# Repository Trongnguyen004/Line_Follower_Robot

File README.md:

# Line_Follower_Robot
## #Hình ảnh

<p align="center">
  <table>
      <td>
        
      </td>
      <td>
        
      </td>
    
  </table>
</p>

### *Cảm biến QTR8A được tham khảo tại: https://www.pololu.com/product/960

<p align="center">
  <table>
    <tr>
      <td>
        
      </td>
      <td>
        
      </td>  
    </tr>
  </table>
</p>

## #Video

### *Chạy Thử

https://github.com/Trongnguyen004/Line_Follower_Robot/assets/137270832/600d7f80-0cda-47ed-8069-f7d0e4e03a02

https://github.com/Trongnguyen004/Line_Follower_Robot/assets/137270832/67cb3d83-4516-45d8-a72a-21b8230ec6d9

### *Test cảm biến
https://github.com/Trongnguyen004/Line_Follower_Robot/assets/137270832/a73f50d7-3c18-4a8b-9868-28da99d4ba61

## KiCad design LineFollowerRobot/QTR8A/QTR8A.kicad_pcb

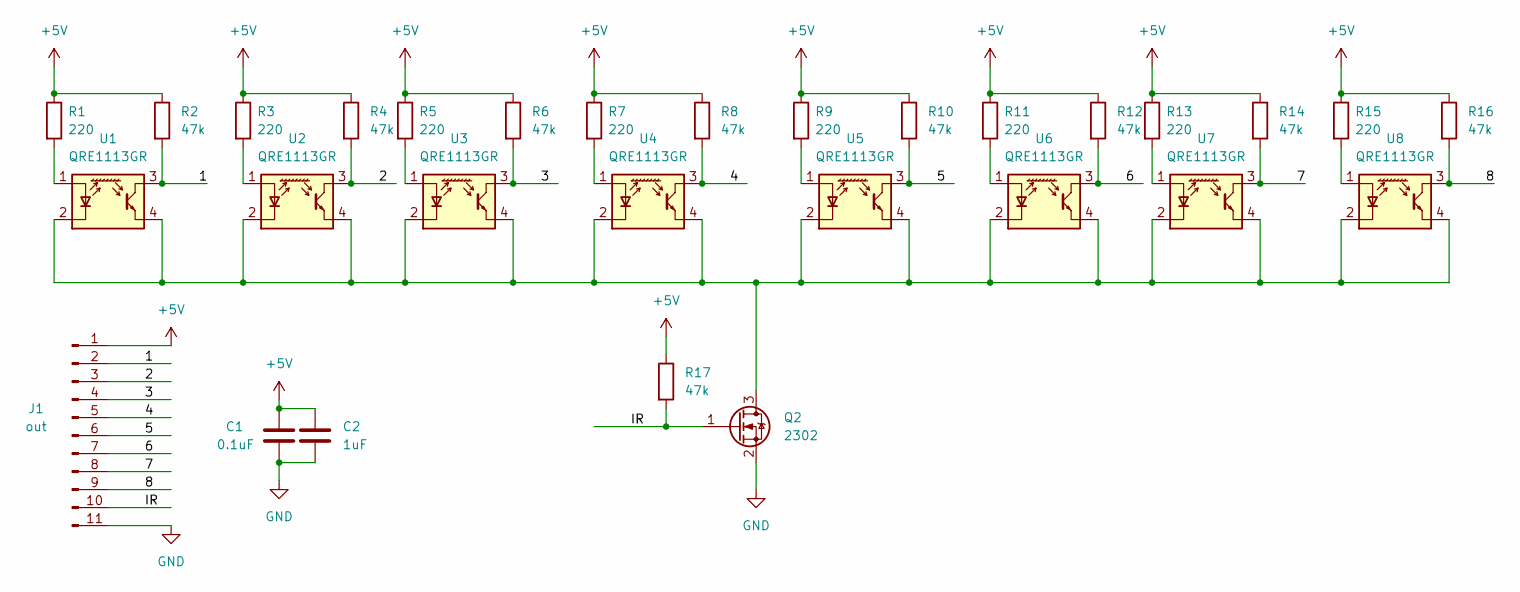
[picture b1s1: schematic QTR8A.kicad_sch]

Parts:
C1: 0.1uF; C_0805_2012Metric
C2: 1uF; C_0805_2012Metric
J1: out; PinHeader_1x11_P2.54mm_Vertical
Q2: 2302; SOT-23
R1, R3, R5, R7, R9, R11, R13, R15: 220; R_0603_1608Metric
R2, R4, R6, R8, R10, R12, R14, R16, R17: 47k; R_0603_1608Metric
U1, U2, U3, U4, U5, U6, U7, U8: QRE1113GR; OnSemi_CASE100CY

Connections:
+5V: C1.1, C2.1, J1.1, R1.1, R2.1, R3.1, R4.1, R5.1, R6.1, R7.1, R8.1, R9.1, R10.1, R11.1, R12.1, R13.1, R14.1, R15.1, R16.1, R17.1
/1: J1.2, R2.2, U1.3
/2: J1.3, R4.2, U2.3
/3: J1.4, R6.2, U3.3
/4: J1.5, R8.2, U4.3
/5: J1.6, R10.2, U5.3
/6: J1.7, R12.2, U6.3
/7: J1.8, R14.2, U7.3
/8: J1.9, R16.2, U8.3
/IR: J1.10, Q2.1 (G), R17.2
GND: C1.2, C2.2, J1.11, Q2.2 (S)
unnamed: Q2.3 (D), U1.2 (K), U1.4, U2.2 (K), U2.4, U3.2 (K), U3.4, U4.2 (K), U4.4, U5.2 (K), U5.4, U6.2 (K), U6.4, U7.2 (K), U7.4, U8.2 (K), U8.4
unnamed: R1.2, U1.1 (A)
unnamed: R3.2, U2.1 (A)
unnamed: R5.2, U3.1 (A)
unnamed: R7.2, U4.1 (A)
unnamed: R9.2, U5.1 (A)
unnamed: R11.2, U6.1 (A)
unnamed: R13.2, U7.1 (A)
unnamed: R15.2, U8.1 (A)

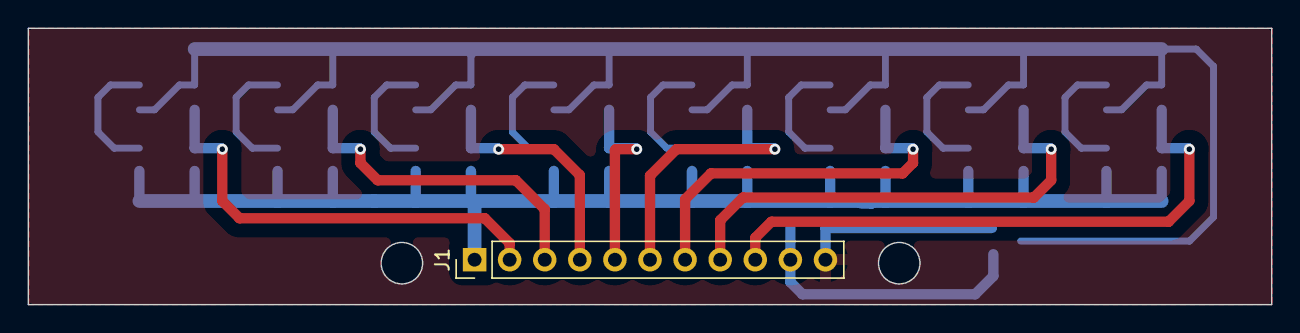
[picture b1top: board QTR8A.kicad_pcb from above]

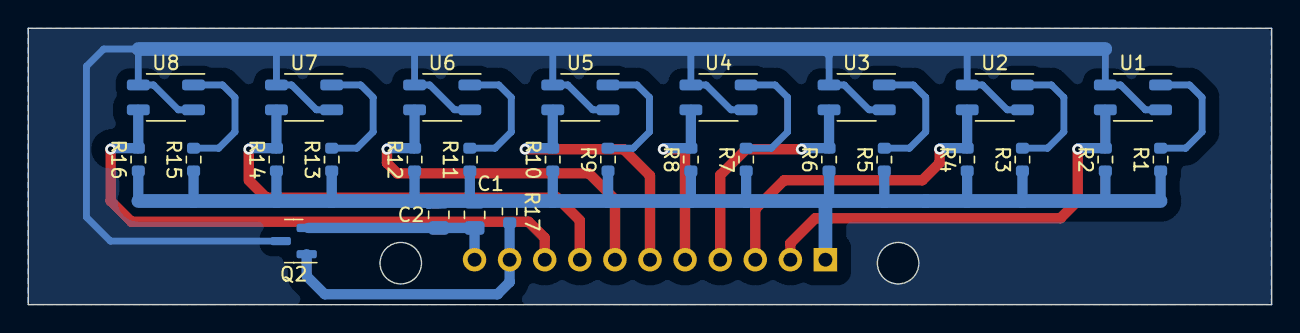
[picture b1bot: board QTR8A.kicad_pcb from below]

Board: 2 copper layers, 90.0 x 20.0 mm, 29 parts (28 on the bottom side), 20 nets.

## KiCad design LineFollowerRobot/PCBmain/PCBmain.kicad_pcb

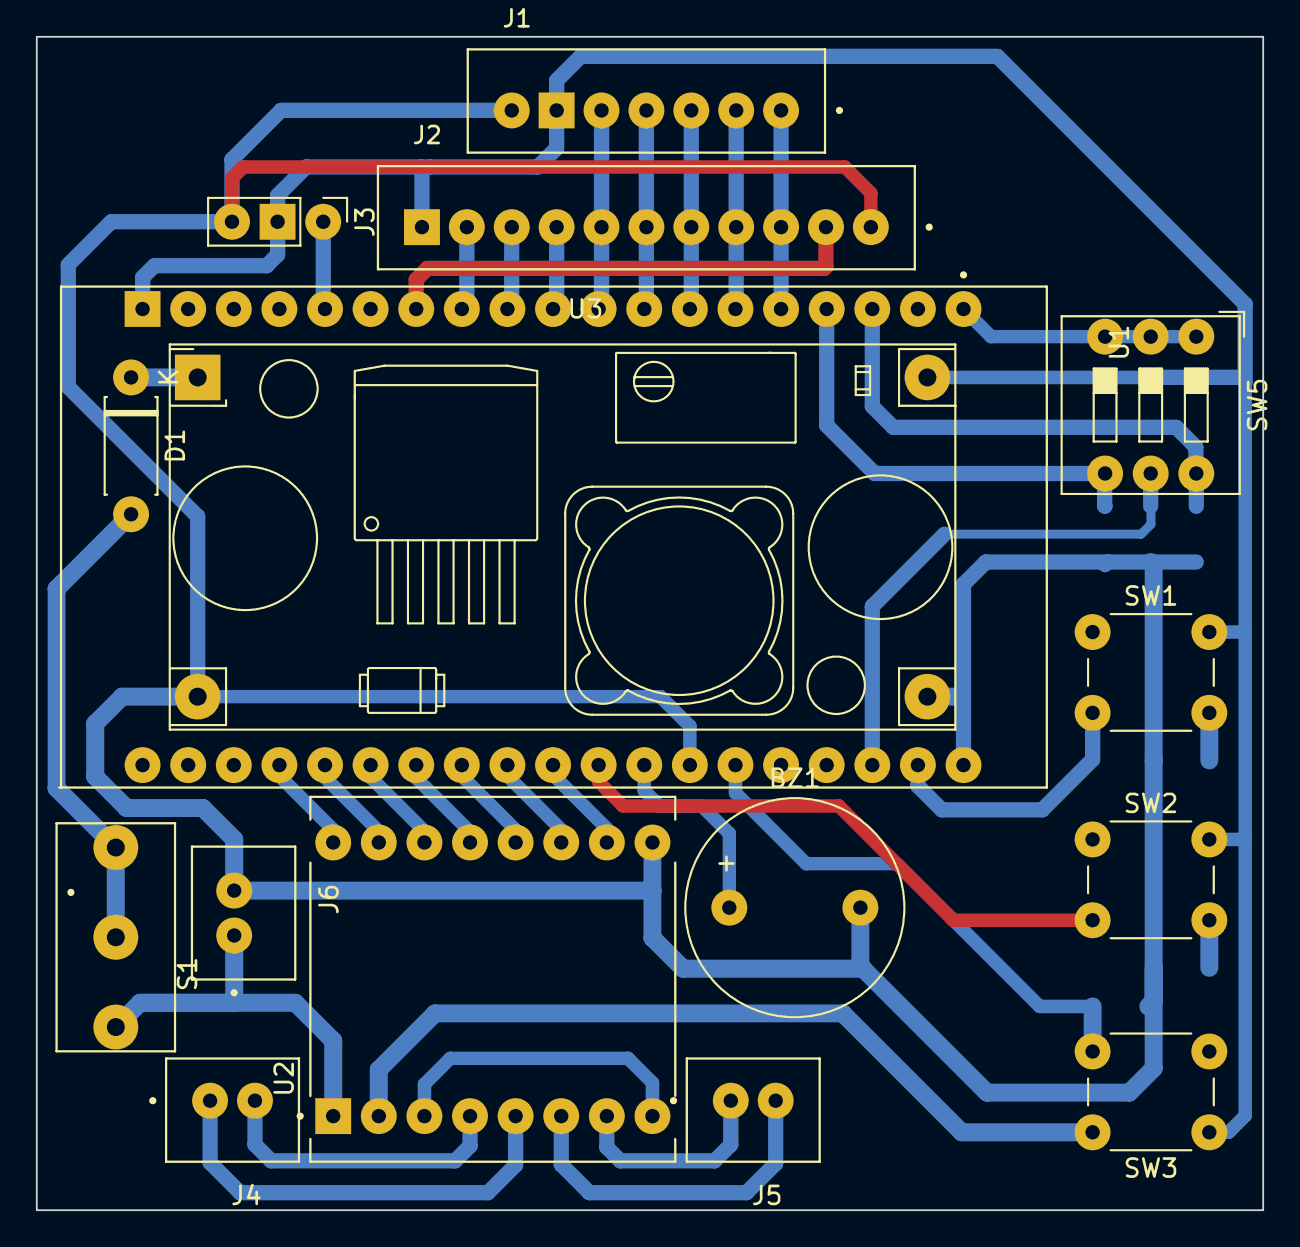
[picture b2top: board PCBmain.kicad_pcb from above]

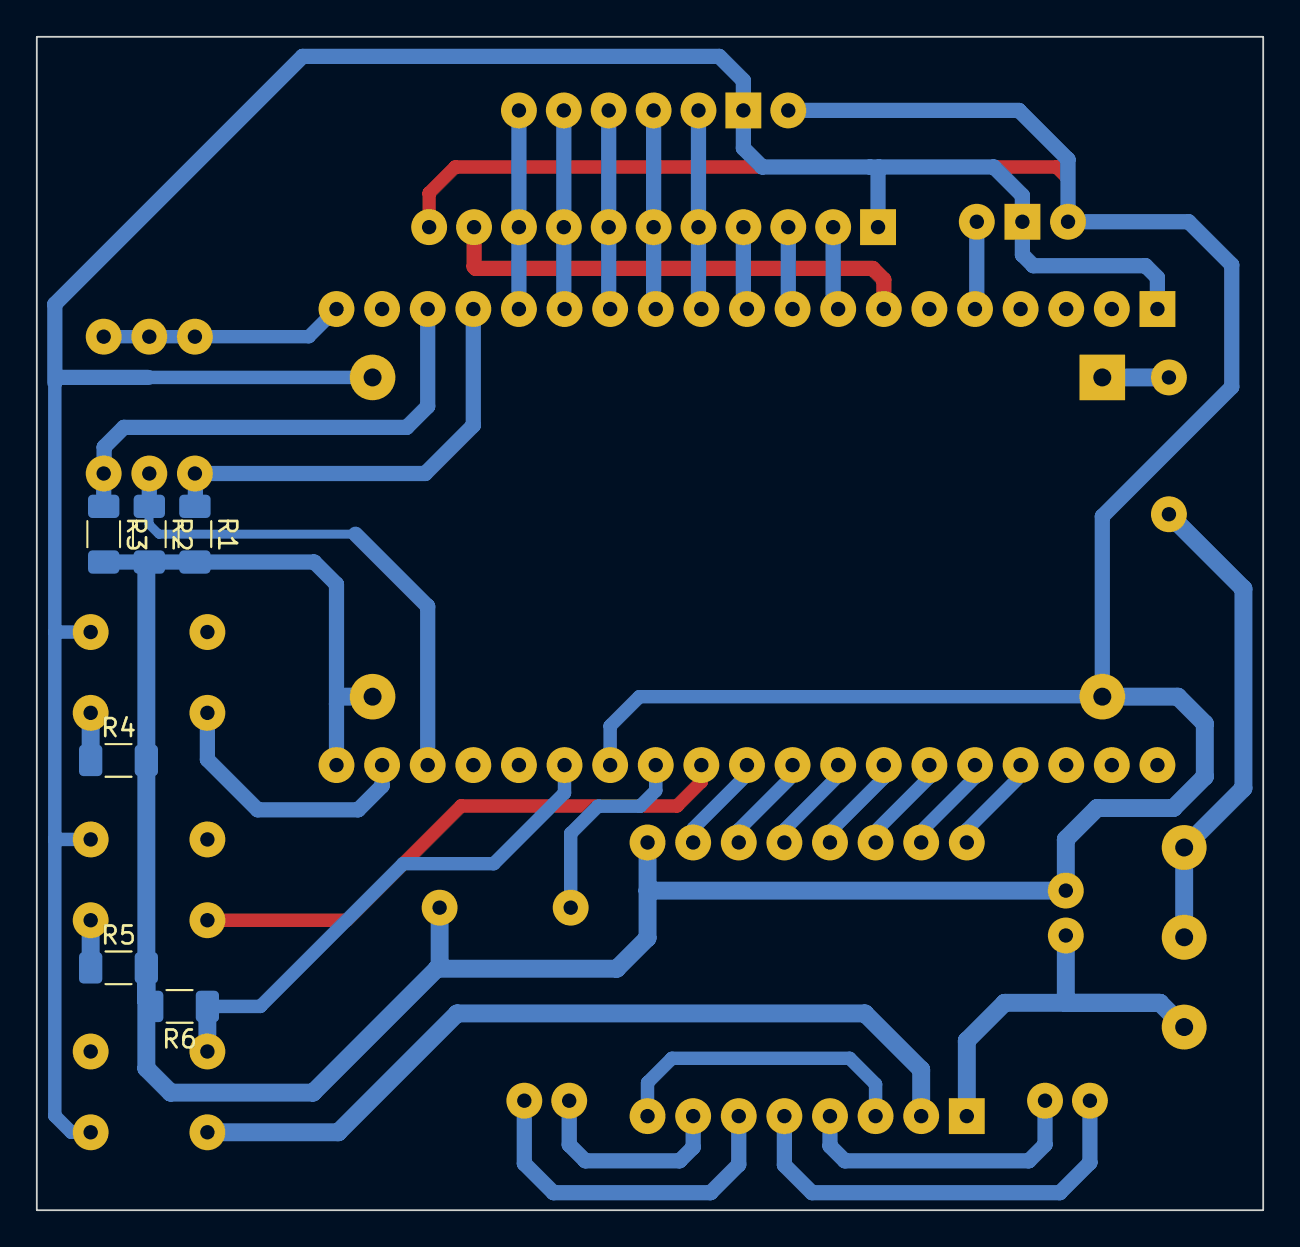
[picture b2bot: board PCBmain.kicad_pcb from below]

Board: 2 copper layers, 68.3 x 65.3 mm, 22 parts (6 on the bottom side), 33 nets.

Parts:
BZ1: Buzzer; Buzzer_12x9.5RM7.6
D1: 1N4007; D_DO-41_SOD81_P7.62mm_Horizontal
J1: JST_B7B-XH-A_LF__SN_
J2: B11B-XH-A_LF__SN_; JST_B11B-XH-A_LF__SN_
J3: Conn_01x03_Pin; PinHeader_1x03_P2.54mm_Vertical
J4, J5: B2B-XH-A_LF__SN_; JST_B2B-XH-A_LF__SN_
J6: connector; JST_B2B-XH-A_LF__SN_
R1, R2, R3, R4, R5, R6: R; R_1206_3216Metric_Pad1.30x1.75mm_HandSolder
S1: công tắc; SW_EG1218
SW1, SW2, SW3: SW_Push; SW_PUSH_6mm_H4.3mm
SW5: SW_DIP_x03; SW_DIP_SPSTx03_Slide_9.78x9.8mm_W7.62mm_P2.54mm
U1: ESP32-DEVKITC-32D; MODULE_ESP32-DEVKITC-32D
U2: TB6612; MODULE_ROB-14450
U3: Module_LM2596; YAAJ_DCDC_StepDown_LM2596

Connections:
+3.3V: SW5.1, SW5.2, SW5.3, U1.J2-1 (3V3)
+5V: J1.6, J2.11, J3.2, SW1.1, SW2.1, SW3.1, U1.J2-19 (EXT_5V), U2.2 (VCC), U3.4 (Vout)
/1: J1.1, J2.3, U1.J2-5 (IO34)
/2: J1.2, J2.4, U1.J2-6 (IO35)
/3: J1.3, J2.5, U1.J2-7 (IO32)
/4: J1.4, J2.6, U1.J2-8 (IO33)
/5: J1.5, J2.7, U1.J2-9 (IO25)
/6: J2.8, U1.J2-10 (IO26)
/7: J2.9, U1.J2-11 (IO27)
/8: J2.10, U1.J2-12 (IO14)
/A: U1.J3-16 (IO15), U2.16 (PWMA)
/A1: U1.J3-14 (IO0), U2.14 (AI1)
/A2: U1.J3-15 (IO2), U2.15 (AI2)
/B: U1.J3-10 (IO5), U2.10 (PWMB)
/B1: U1.J3-12 (IO16), U2.12 (BI1)
/B2: U1.J3-11 (IO17), U2.11 (BI2)
/But1: R4.1, SW1.2, U1.J3-2 (IO23)
/But2: R5.1, SW2.2, U1.J3-9 (IO18)
/But3: R6.1, SW3.2, U1.J3-6 (IO21)
/Buzz: BZ1.1 (-), U1.J3-8 (IO19)
/IR: J2.2, U1.J2-13 (IO12)
/STBY: U1.J3-13 (IO4), U2.13 (STBY)
/SW1: R1.1, SW5.4, U1.J2-4 (SENSOR_VN)
/SW2: R2.1, SW5.5, U1.J3-3 (IO22)
/SW3: R3.1, SW5.6, U1.J2-3 (SENSOR_VP)
GND: BZ1.2 (+), J1.7, J2.1, J3.3, J6.2, R1.2, R2.2, R3.2, R4.2, R5.2, R6.2, U1.J2-14 (GND1), U1.J3-1 (GND3), U1.J3-7 (GND2), U2.3 (GND), U2.8 (GND), U2.9 (GND), U3.2 (GND), U3.3 (GND)
unnamed: D1.2 (A), S1.1, S1.2
unnamed: D1.1 (K), U3.1 (Vin)
unnamed: J4.2, U2.4 (A01)
unnamed: J4.1, U2.5 (A02)
unnamed: J5.1, U2.7 (B01)
unnamed: J5.2, U2.6 (B02)
VCC: J6.1, S1.3, U2.1 (VM)
